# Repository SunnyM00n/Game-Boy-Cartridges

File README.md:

# Game Boy Cartridge Circuit Boards

This is a repository listing all of my Game Boy game circuit board variants. <a href="https://github.com/MouseBiteLabs/Game-Boy-Cartridges/wiki">Also be sure to check out the wiki for more information.</a>

## Game Boy Board Links

| **Board Name**                                                                                                                | **Board Number**   | **Max ROM Size**       | **Max RAM Size**  | **Multicart Support?** | **Memory Family Used**          |
|-------------------------------------------------------------------------------------------------------------------------------|--------------------|------------------------|-------------------|------------------------|---------------------------------|
| <a href="https://github.com/MouseBiteLabs/Game-Boy-MBC1-Cartridge">MBC1 (Type B)</a>                                          | GB-4DV4S-01B       | 4 MB                   | 32 KB             | No                     | Type B (29F016, 29F032, 29F033) |
| <a href="https://github.com/MouseBiteLabs/Game-Boy-MBC3-Cartridge">MBC3 (Type B)</a>                                          | GB-4KV4S-01B       | 4 MB                   | 32 KB             | No                     | Type B (29F016, 29F032, 29F033) |
| <a href="https://github.com/MouseBiteLabs/Game-Boy-MBC5-Cartridge">MBC5 (Type B)</a>                                          | GB-4AV8S-01B       | 4 MB                   | 128 KB            | No                     | Type B (29F016, 29F032, 29F033) |
| <a href="https://github.com/MouseBiteLabs/Game-Boy-Cartridges/tree/main/MBC3%20Multicart">MBC3 Multicart (Type B)</a>         | GB-4KV8Q-01B       | 4 MB (2x 2 MB, 4x 1MB) | 128 KB (4x 32 KB) | Yes                    | Type B (29F032, 29F033)         |
| <a href="https://github.com/MouseBiteLabs/Game-Boy-Cartridges/tree/main/MBC5%20Multicart">MBC5 Multicart (Type B)</a>         | GB-4AV8Q-01B       | 4 MB (2x 2 MB, 4x 1MB) | 128 KB (4x 32 KB) | Yes                    | Type B (29F032, 29F033)         |
| <a href="https://github.com/MouseBiteLabs/Game-Boy-Cartridges/tree/main/MBC1%20(Type%20A%2C%20SRAM)">MBC1 (Type A)</a>        | GB-2DV4S-01A       | 2 MB                   | 32 KB             | No                     | Type A (M29F160)                |
| <a href="https://github.com/MouseBiteLabs/Game-Boy-Cartridges/tree/main/MBC3%20(Type%20A%2C%20SRAM)">MBC3 (Type A)</a>        | GB-2KV4S-01A       | 2 MB                   | 32 KB             | No                     | Type A (M29F160)                |
| <a href="https://github.com/MouseBiteLabs/Game-Boy-Cartridges/tree/main/MBC5%20(Type%20A%2C%20SRAM)">MBC5 (Type A)</a>        | GB-2AV8S-01A       | 2 MB                   | 128 KB            | No                     | Type A (M29F160)                |
| MBC1 (Type A, FRAM)                                                                                                           | GB-2DF4S-01A       | 2 MB                   | 32 KB             | No                     | Type A (M29F160)                |
| <a href="https://github.com/MouseBiteLabs/Game-Boy-Cartridges/tree/main/MBC3%20(Type%20A%2C%20FRAM)">MBC3 (Type A, FRAM)</a>  | GB-2KF4S-01A       | 2 MB                   | 32 KB             | No                     | Type A (M29F160)                |
| <a href="https://github.com/MouseBiteLabs/Game-Boy-Cartridges/tree/main/MBC5%20(Type%20A%2C%20FRAM)">MBC5 (Type A, FRAM)</a>  | GB-2AF4S-01A       | 2 MB                   | 32 KB             | No                     | Type A (M29F160)                |

## Naming Convention

| GB       | \- | 2                 | A               | V              | 4            | S                                            | \- | 01       | A                                       |
| -------- | -- | ----------------- | --------------- | -------------- | ------------ | -------------------------------------------- | -- | -------- | --------------------------------------- |
| Game Boy |    | Max ROM Size (MB) | Mapper Chip     | SRAM or FRAM?  | Max RAM Size | Multicart Support                            |    | Revision | Memory Family                           |
|          |    | 1                 | N = None        | X = None       | 0 = None     | S = Single game                              |    |          | A = New EEPROM (M29F160)                |
|          |    | 2                 | D = MBC1        | V = SRAM       | 1 = 2 KB     | D = Multicart (2x, split max ROM/RAM space)  |    |          | B = NOS EEPROM (29F016, 29F032, 29F033) |
|          |    | 4                 | K = MBC3        | F = FRAM       | 2 = 8 KB     | Q = Multicart (4x, split max ROM/RAM space)  |    |          |                                         |
|          |    | 6                 | A = MBC5        |                | 4 = 32 KB    |                                              |    |          |                                         |
|          |    | 8                 |                 |                | 8 = 128 KB   |                                              |    |          |                                         |

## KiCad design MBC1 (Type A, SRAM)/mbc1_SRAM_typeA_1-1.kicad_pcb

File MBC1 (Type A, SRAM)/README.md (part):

# Game Boy MBC1 Cartridge - Type A, SRAM

This is an updated design of my flashable MBC1-based cartridge for the Game Boy. The MBC1 mapper was used in many of the earlier Game Boy games, such as the Super Mario Land series, the Donkey Kong Land series, Metroid II, and one of my personal favorites - the original Link's Awakening. 

**This MBC1 cartridge uses brand new M29F160 EEPROM chips and battery-backed SRAM.**

This circuit board should cover most, if not all, MBC1 games. The features are as follows:

- Able to make games that use 512 KB (4 Mbit) of ROM and 256 Kbit of RAM, or 2 MB (16 Mbit) of ROM and 64 Kbit of RAM
- Compatibility with all four of the major Game Boy battery management ICs - MM1026, MM1134, BA6129, and BA6735
- The option to add battery backup to the cartridge *without* the need of the original battery management ICs - perfect for MBC1 donors that didn't have batteries in them
- Lower battery consumption compared to some of the original cartridges
- Fully compatible with the <a href="https://www.gbxcart.com/">GBxCart RW</a> so you can transfer games and save files to and from the board

All gerbers and source files can be found in this repo, as this project is fully open source **with attribution**.

## Important Version Note!

An error with v1.0 boards does not let you flash games on an assembled cart with the RAM set to 64K mode. Functionally, this means you cannot flash game ROMs larger than 512Kbit. I can find only one game that fits this category, so this should be a very minor issue. 

**You must put the cartridge in 256K SRAM mode in order to flash any game using a cart flasher like the GBxCart. Once your game is flashed, change the RAM mode to 64K if your game requires it.** You can also flash the ROM to the M29F160 separately, and then solder it onto the board, to get around this issue.

Version 1.1 should fix this error, but it has not been tested yet. I am waiting for the order of boards to arrive so I may test it.

## Important Things Before You Start

1) To use this board, you need to have an original Game Boy game that uses an MBC1 mapper chip. <a href="https://catskull.net/gb-rom-database/">You can find a list of games and their mappers here</a>. Use the search function. Please note the RAM is in bytes, not bits. Since SRAM in this repo is defined in bits, you need to convert by multiplying the number of bytes by 8.
2) You will need to remove the MBC1 from your donor cartridge for use on this board. This will require a hot air rework station or a hot plate. There's a list below of other parts you can re-use from the donor cartridge.
3) When soldering parts on, it's a good idea to put kapton tape or otherwise cover the bottom cartridge edge. You do not want to get solder on the cartridge contacts.
4) I am not responsible for any damage you do to your self or your property. Attempt this project at your own risk.
5) I do not guarantee design compatibility. You may encounter issues with certain games. There is also a chance I have made an error in the design or the BOM - if this is the case, I will do everything I can to address the problem as quickly as possible.
6) If you are using this board to make games other than for personal use, you must have permission from the originator to use and distribute any ROM images or other related material. You are responsible for making sure you adhere to any license requirements.

DO NOT use my circuit boards for profiting from stolen work - this especially includes homebrew content, ROM hacks, and using fan-made labels without permission from the originator. **Support original creators!**

## Board Characteristics and Order Information

The zipped folder contains all the gerber files for this board. The following options **must** be chosen when ordering boards for yourself.

- Thickness: 0.8mm
- Surface Finish: ENIG
- Gold Fingers: Yes, 30° chamfer

**I sell this blank circuit board on Etsy, so you don't have to buy a bunch of multiples if you don't want to.** (Click the banner!)

You can use the zipped folder at any board fabricator you like. You may also buy the board from PCBWay using this link (disclosure: I receive 10% of the sale value to go twoards future PCB orders of my own):

<a href="https://oshpark.com/shared_projects/nTwQT1IF">The board is also listed on OSH Park as well.</a> **Be sure to get them in 0.8mm thickness if you order from here.**

## Required Equipment

The EEPROM on the board needs to be programmed somehow. There are a few options for doing this:

1) <a href="https://www.gbxcart.com/">**GBxCart**</a>. This is a perfect option if you want an easy way to make Game Boy cartridges without a lot of extra effort. This is a standalone flasher that plugs into your computer via USB. The cartridge circuit board is fully compatible with it, and it makes reflashing games extremely easy using <a href="https://github.com/lesserkuma/FlashGBX">lesserkuma's FlashGBX software</a>.
2) At the lowest level, you can buy an EEPROM programmer with a TSOP chip programming adapter. The downside to this method is that you have to desolder the chip every time you want to program it. The <a href="https://flashcatusb.com/">FlashcatUSB</a> is one popular option in retro spaces, but I use the <a href="https://xgecu.myshopify.com/products/xgecu-new-t48-tl866-3gprogrammer-v12-01-support-28000-ics-for-spi-nor-nand-flash-emmc-bga153-162-169-100-221-tsop-sop-plcc">T48 programmer</a> with the <a href="https://xgecu.myshopify.com/products/100-original-xgecu-adp_f48_ex-1-tsop48-special-adapter-for-nor-flash-only-use-on-t48-tl866-3g-programmer">TSOP48 adapter</a>.

### How to Program the Cartridges

<a href="https://github.com/MouseBiteLabs/Game-Boy-Cartridges/wiki">Check out the wiki for more information.</a>

## Battery Safety

When assembling a board, I recommend populating all the parts *except* the battery, and getting it to run initially without it. This is to make it easier to fix any solder connections that might need fixing, without having to worry about getting the battery hot. And if you need to rework anything near the battery after you've put it on the board, be safe and remove it before putting a hot soldering iron next to it.

If you're assembling these boards with a hot plate or hot air, *do not* solder the battery on this way. You should use an iron, and keep heat off of the battery as much as possible. 

(Also check polarity!)

## Board Configurations

The board comes with four sets of jumper pads for solder bridges. SJ1 and SJ2 require you to solder bridge the middle pad either to the top pad or the bottom pad. SJ3 and SJ4 are configured by either leaving them alone or bridging them with solder. Here are the situations where you need to add solder bridges.

**<a href="https://github.com/MouseBiteLabs/Game-Boy-Cartridges/wiki/MBC1">You can check out the wiki for some pictures of boards in various configurations to follow along with.</a>**

### RAM Size Selection (SJ1/SJ2, or SW1)

These two sets of pads are labelled "RAM SIZE" in the middle of the board. Soldering them will configure the max RAM *and* ROM size. You must configure these pads for every game you make - do not leave them empty (if you have no SRAM, solder to the "64K" setting to maximize ROM space). <a href="https://catskull.net/gb-rom-database/">You can find a list of games here with their respective ROM and RAM sizes.</a>

**As stated earlier, on v1.0 boards, the RAM size selection must be in 256K mode to flash your ROM file with a cart flasher.**

- Solder bridge SJ1 and SJ2 from their middle pads to the top pads for games that have larger ROM sizes (up to 2 MB, or 16 Mbit of ROM, and up to 64 Kbit of RAM).

- Solder bridge SJ1 and SJ2 from their middle pads to the bottom pads for games that have larger RAM sizes (up to 512 KB, or 4 Mbit of ROM, and up to 256 Kbit of RAM).

- SJ1 and SJ2 must be soldered in the same direction.

- The footprint of these selection pads should allow for a DPDT switch, part number CAS-220A1, to be placed on these pads instead of having to bridge the pads with solder.

### Using an MM1134 or BA6735 for U4 (SJ3)

Bridge the jumper SJ3 if you have either an MM1134 or BA6735 for U4, specifically. Any other battery management IC must leave SJ3 unsoldered.

### Making Games Without RAM (SJ1/SJ2, SJ4)

If your game does not have RAM on it (and therefore, you don't need the battery management IC U4), bridge SJ4 with solder. **Do not** bridge SJ4 if you are using U5 (TPS3613) instead of U4.

You also should solder the SRAM size selection to the 64K setting.

## Test Points and Final Checkout

On the back of the board are five test points. Here's where they are connected:

- TP1: SRAM supply voltage
- TP2: Battery voltage (after R1)
- TP3: Battery voltage (positive terminal of battery)
- TP4: Ground
- TP5: VCC input voltage

After you assemble your game, you should measure the current out of the battery. But first, you should program it with the GBxCart, or if you programmed the EEPROM separately, put it into a Game Boy and cycle power once. Then, flip the PCB upside down on a non-conductive surface (not your leg), and set your multimeter in DC millivolts (or volts). Put the positive probe on TP3 and the negative probe on TP2. If you used a 10kΩ for R1, as indicated in the BOM, you should read a voltage in the single of millivolts. If you have something much higher, especially voltages above 20mV, then you likely have an issue or short circuit on the board somewhere.

**Note: You need to power up the game at least once before battery currents will make sense - the battery management ICs can start up in an unknown state before applying main power to the board.**

To estimate battery life, see <a href="https://github.com/MouseBiteLabs/Game-Boy-MBC1-Cartridge/tree/main/Technical#estimating-battery-life">this section in the Technical Design Document of my first MBC1 design</a>, or for more in-depth analysis, <a href="https://hackaday.io/project/11864-tritiled/log/72554-determining-maximum-runtime-176-to-202-years-cr2032">this Hackaday post</a>.

## Board Fitment

The shape of this board was originally meant to mimic original Game Boy circuit boards as closely as possible. Unfortunately, when placed in some aftermarket Game Boy cartridge shells (like those from Cloud Game Store), the circuit board has a lot of freedom to rotate around the main screw hole in the bottom-middle of the cartridge. This can cause misalignment when you put it in a Game Boy, which can cause a game to either not load properly (garbled Game Boy logo) or shut off the Game Boy because of a short circuit. This isn't *dangerous* or anything, just annoying.

In order to make the boards fit nicer in any kind of shell, I added extended tabs of circuit board material to the edges of the cartridges to keep it from rotating too much in shells, which was suggested to me by <a href="https://github.com/orangeglo">orangeglo</a>! (Thanks!)

If you're having trouble fitting the circuit board into a shell, because the tabs interfere with the cart edges, you can safely sand or trim them down as there is no copper within the tabs themselves. The only shell that appears to require any kind of trimming are Kitsch-Bent shells.

## Bill of Materials (BOM)

Your parts list will vary depending on the game you are trying to make, and what chips you have for the battery management (if any). **You cannot use both U4 and U5 - you must choose one or the other.** U4 comes from a donor cartridge, and U5 is a readily available aftermarket option.

Please carefully review the parts you need for the board you are trying to make. Do not add any parts to your build that don't appear in the column for the game you are making. This means you *cannot* populate every component on the board at the same time.

| Reference Designators | Value/Part Number              | Package          | Description        | No save carts | Save carts with MM1134 or BA6735 | Save carts with MM1026 or BA6129 | Save carts without donor U4 chip | Source                                           |
| --------------------- | ------------------------------ | ---------------- | ------------------ | ------------- | -------------------------------- | -------------------------------- | -------------------------------- | ------------------------------------------------ |
| B1                    | CR2032, CR2025, CR2016         | CR2032           | Backup Battery     |               | x                                | x                                | x                                | [https://mou.sr/3SeAzfT](https://mou.sr/3SeAzfT) |
| C1                    | 0.1uF                          | 0603             | Capacitor (MLCC)   | x             | x                                | x                                | x                                | [https://mou.sr/3ENc15O](https://mou.sr/3ENc15O) |
| C4                    | 0.1uF                          | 0603             | Capacitor (MLCC)   |               | x                                | x                                |                                  | [https://mou.sr/3ENc15O](https://mou.sr/3ENc15O) |
| C5                    | 0.1uF                          | 0603             | Capacitor (MLCC)   |               | x                                | x                                | x                                | [https://mou.sr/3ENc15O](https://mou.sr/3ENc15O) |
| C6                    | 10uF                           | 0603             | Capacitor (MLCC)   |               | x                                | x                                | x                                | [https://mou.sr/3mZtSkF](https://mou.sr/3mZtSkF) |
| C7                    | 0.1uF                          | 0603             | Capacitor (MLCC)   | x             | x                                | x                                | x                                | [https://mou.sr/3ENc15O](https://mou.sr/3ENc15O) |
| C8                    | 0.1uF                          | 0603             | Capacitor (MLCC)   |               |                                  |                                  | x                                | [https://mou.sr/3ENc15O](https://mou.sr/3ENc15O) |
| Q1                    | 2N7002                         | SOT-23           | N-Channel FET      |               |                                  |                                  | x                                | [https://mou.sr/3rgfh6J](https://mou.sr/3rgfh6J) |
| Q2                    | 2N7002                         | SOT-23           | N-Channel FET      |               |                                  | x                                |                                  | [https://mou.sr/3rgfh6J](https://mou.sr/3rgfh6J) |
| R1                    | 10k                            | 0603             | Resistor           |               | x                                | x                                | x                                | [https://mou.sr/3riR7IH](https://mou.sr/3riR7IH) |
| R3                    | 49.9k                          | 0603             | Resistor           |               | x                                | x                                | x                                | https://mou.sr/3Q3NRZO                           |
| R4                    | 49.9k                          | 0603             | Resistor           |               | x                                | x                                | x                                | https://mou.sr/3Q3NRZO                           |
| R5                    | 49.9k                          | 0603             | Resistor           |               | x                                | x                                | x                                | https://mou.sr/3Q3NRZO                           |
| R6                    | 49.9k                          | 0603             | Resistor           |               | x                                | x                                | x                                | https://mou.sr/3Q3NRZO                           |
| R7                    | 10k                            | 0603             | Resistor           |               |                                  | x                                |                                  | [https://mou.sr/3riR7IH](https://mou.sr/3riR7IH) |
| R8                    | 10k                            | 0603             | Resistor (v1.1 and later) | x      | x                                | x                                | x                                | [https://mou.sr/3riR7IH](https://mou.sr/3riR7IH) |
| R9                    | 130k                           | 0603             | Resistor           |               |                                  |                                  | x                                | https://mou.sr/3MjXliy                           |
| R10                   | 49.9k                          | 0603             | Resistor           |               |                                  |                                  | x                                | https://mou.sr/3Q3NRZO                           |
| U1                    | M29F160                        | TSOP-48          | Flash EEPROM       | x             | x                                | x                                | x                                | [https://mou.sr/3N0a9eL](https://mou.sr/3N0a9eL) |
| U2                    | MBC1                           | SOP-24           | MBC1 Mapper        | x             | x                                | x                                | x                                | Donor MBC1 Game Boy cartridge                    |
| U3                    | AS6C6264, AS6C62256            | SOP-28           | SRAM               |               | x                                | x                                | x                                | [https://mou.sr/450klcY](https://mou.sr/450klcY) |
| U4                    | MM1026, MM1134, BA6129, BA6735 | SOIC-8           | Battery Management |               | x                                | x                                |                                  | Donor Game Boy cartridge                         |
| U5                    | TPS3613                        | MSOP-10          | Battery Management |               |                                  |                                  | x                                | https://mou.sr/45Ir2kh                           |

*Note that C9 - C11 footprints are only included on the board for strange edge cases that may require them sometime in the future; do not populate! See the technical design document for more information.*

### Usable Donor Cartridge Parts

You can use a few parts from the donor cart on the new board to save some money. Note that you will generally get better reliability with new parts as opposed to old ones. For example: I have seen failed RAM chips from donors in the past.

1) **U2: MBC1** - This one is required
2) **U3: SRAM** - You can use this part *only if* the game you're making uses the same or less amount of RAM that the donor cartridge does
3) **U4: Battery Management IC** - Using this is probably preferred over the TPS3613 because it'll save you money and parts to put on

You could probably transfer over most of the 0.1uF capacitors but they're pretty cheap anyway, so I generally just recommend buying new resistors and capacitors.

## Things to Remember

- The footprint for the battery can fit a CR2032, CR2025, or CR2016 with solder tabs. The only difference is the mAh capacity (larger number = longer life). If you get Panasonic tabbed batteries, you may have to trim the battery tabs to make them fit on the footprint.
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
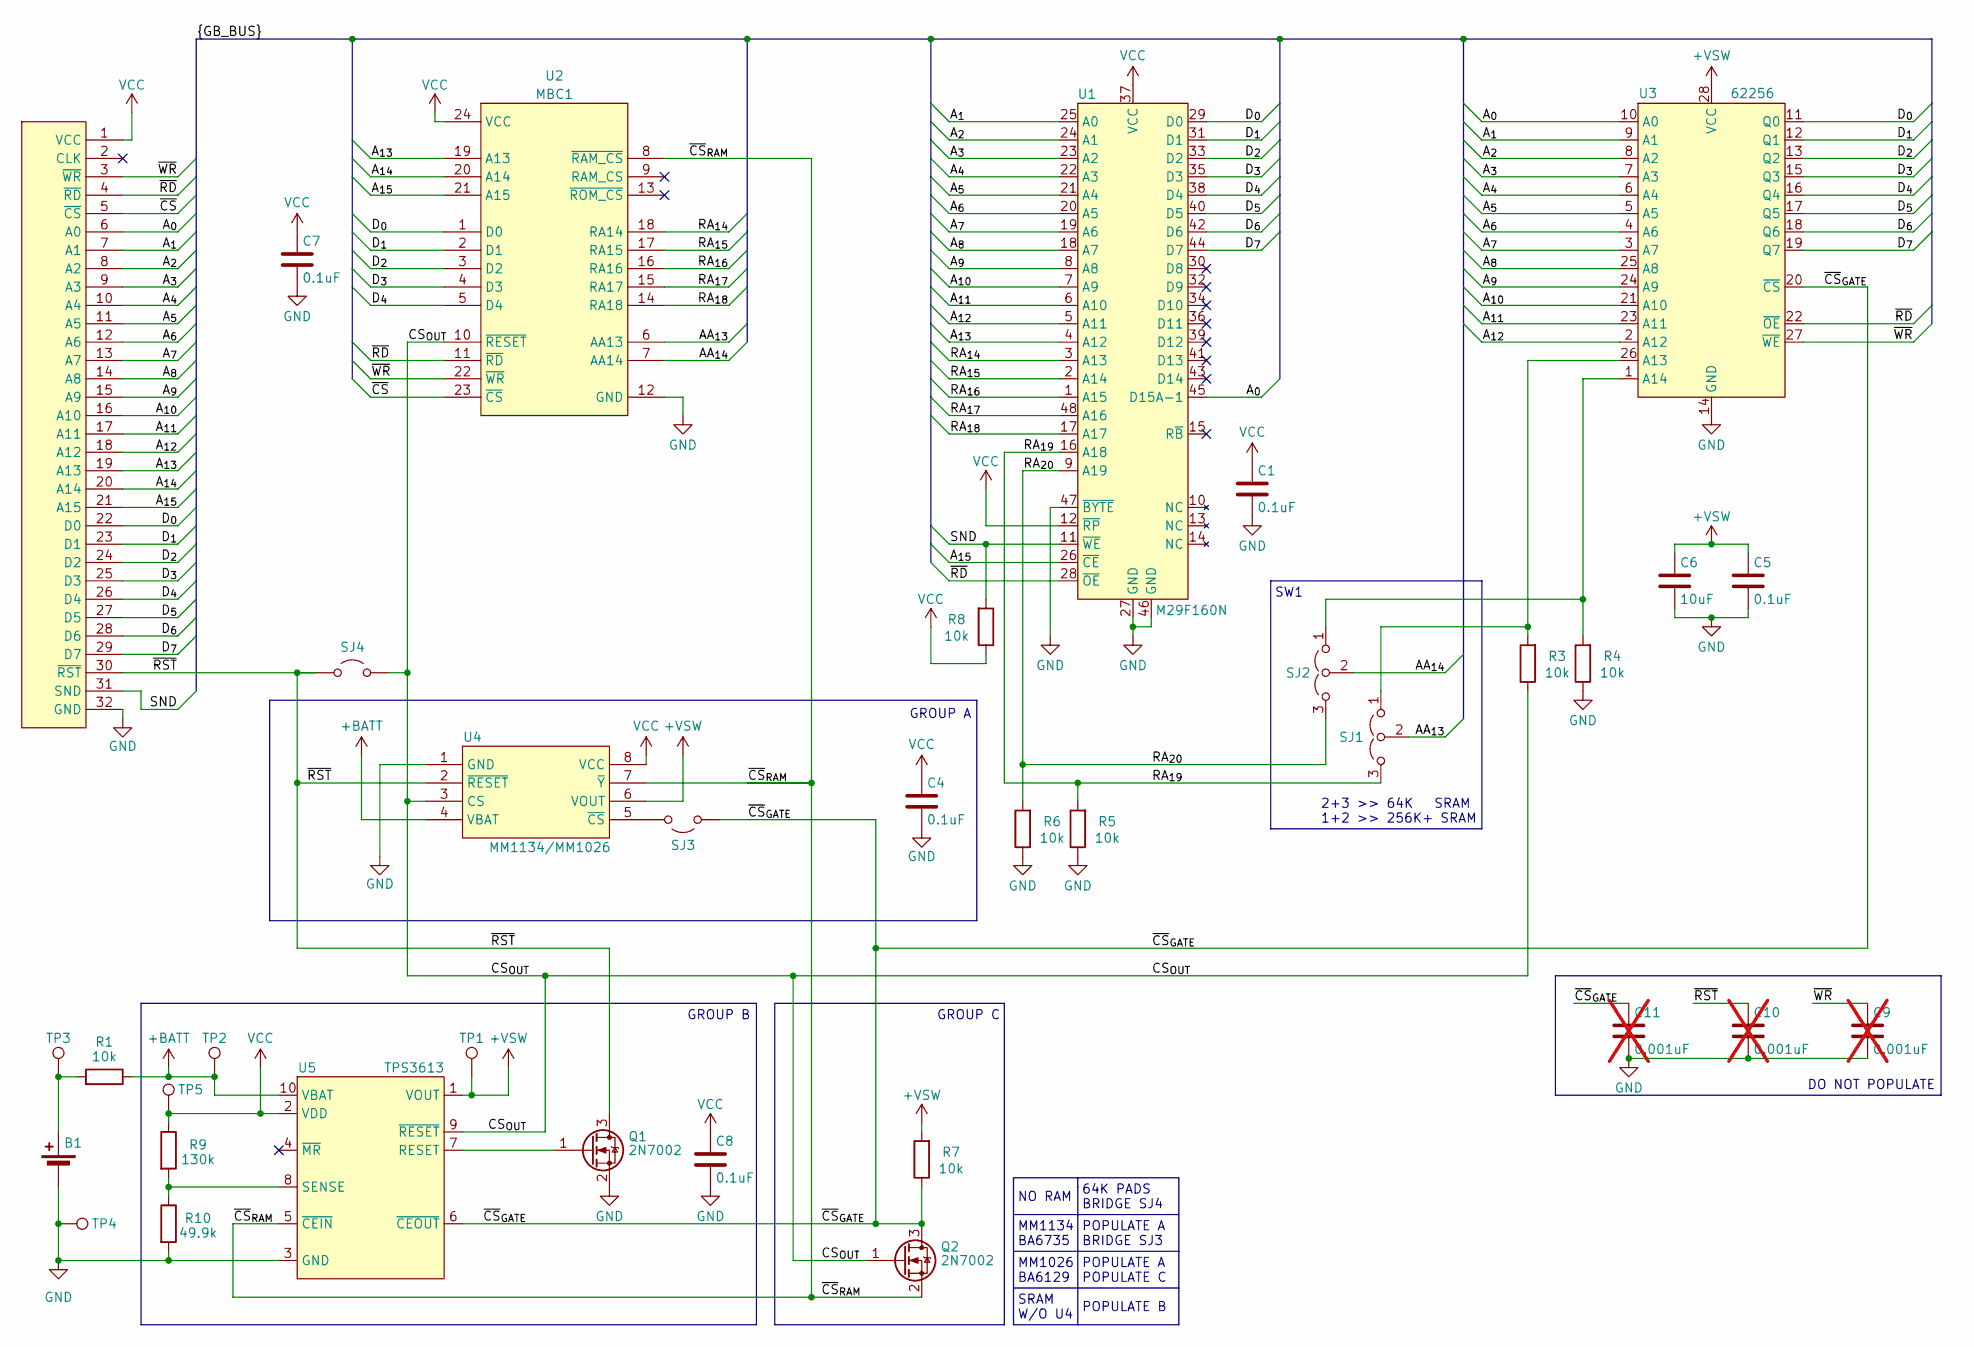
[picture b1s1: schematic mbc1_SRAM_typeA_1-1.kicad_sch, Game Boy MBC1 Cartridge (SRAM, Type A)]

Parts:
B1: CR2025
C1, C4, C5, C7, C8: 0.1uF; C_0603_1608Metric_Boxed
C6: 10uF; C_0603_1608Metric_Boxed
C9, C10, C11: 0.001uF; C_0603_1608Metric_Boxed; not fitted
P1: GBC_CARTTAB; GBC_CART_TABBED
Q1, Q2: 2N7002; SOT-23
R1, R3, R4, R5, R6, R7, R8: 10k; R_0603_1608Metric_Boxed
R9: 130k; R_0603_1608Metric_Boxed
R10: 49.9k; R_0603_1608Metric_Boxed
SJ1, SJ2: SJ2W; SJ_2
SJ3, SJ4: SJ
TP1, TP2, TP3, TP4, TP5: TPB1,27; TestPoint_Pad_D1.0mm
U1: M29F160N; TSOP-I-48_18.4x12mm_P0.5mm
U2: MBC1; SO24
U3: 62256; SO28
U4: MM1134/MM1026; SOIC-8_3.9x4.9mm_P1.27mm
U5: TPS3613; MSOP-10_3x3mm_P0.5mm

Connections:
+BATT: R1.1, TP2.1, U4.4 (VBAT), U5.10 (VBAT)
+VSW: C5.1, C6.1, R7.2, TP1.1, U3.28 (VCC), U4.6 (VOUT), U5.1 (VOUT)
/AA_{13}: SJ1.2 (C), U2.6 (AA13)
/AA_{14}: SJ2.2 (C), U2.7 (AA14)
/A_{0}: P1.6 (A0), U1.45 (D15A-1), U3.10 (A0)
/A_{1}: P1.7 (A1), U1.25 (A0), U3.9 (A1)
/A_{2}: P1.8 (A2), U1.24 (A1), U3.8 (A2)
/A_{3}: P1.9 (A3), U1.23 (A2), U3.7 (A3)
/A_{4}: P1.10 (A4), U1.22 (A3), U3.6 (A4)
/A_{5}: P1.11 (A5), U1.21 (A4), U3.5 (A5)
/A_{6}: P1.12 (A6), U1.20 (A5), U3.4 (A6)
/A_{7}: P1.13 (A7), U1.19 (A6), U3.3 (A7)
/A_{8}: P1.14 (A8), U1.18 (A7), U3.25 (A8)
/A_{9}: P1.15 (A9), U1.8 (A8), U3.24 (A9)
/A_{10}: P1.16 (A10), U1.7 (A9), U3.21 (A10)
/A_{11}: P1.17 (A11), U1.6 (A10), U3.23 (A11)
/A_{12}: P1.18 (A12), U1.5 (A11), U3.2 (A12)
/A_{13}: P1.19 (A13), U1.4 (A12), U2.19 (A13)
/A_{14}: P1.20 (A14), U2.20 (A14)
/A_{15}: P1.21 (A15), U1.26 (~CE), U2.21 (A15)
/CS_{OUT}: Q2.1 (G), R3.1, SJ4.2 (B), U2.10 (~RESET), U4.3 (CS), U5.9 (~RESET)
/D_{0}: P1.22 (D0), U1.29 (D0), U2.1 (D0), U3.11 (Q0)
/D_{1}: P1.23 (D1), U1.31 (D1), U2.2 (D1), U3.12 (Q1)
/D_{2}: P1.24 (D2), U1.33 (D2), U2.3 (D2), U3.13 (Q2)
/D_{3}: P1.25 (D3), U1.35 (D3), U2.4 (D3), U3.15 (Q3)
/D_{4}: P1.26 (D4), U1.38 (D4), U2.5 (D4), U3.16 (Q4)
/D_{5}: P1.27 (D5), U1.40 (D5), U3.17 (Q5)
/D_{6}: P1.28 (D6), U1.42 (D6), U3.18 (Q6)
/D_{7}: P1.29 (D7), U1.44 (D7), U3.19 (Q7)
/RA_{14}: U1.3 (A13), U2.18 (RA14)
/RA_{15}: U1.2 (A14), U2.17 (RA15)
/RA_{16}: U1.1 (A15), U2.16 (RA16)
/RA_{17}: U1.48 (A16), U2.15 (RA17)
/RA_{18}: U1.17 (A17), U2.14 (RA18)
/RA_{19}: R5.2, SJ1.3 (B), U1.16 (A18)
/RA_{20}: R6.2, SJ2.3 (B), U1.9 (A19)
/SND: P1.31 (SND), R8.2, U1.11 (~WE)
/~CS: P1.5 (~CS), U2.23 (~CS)
/~CS_{GATE}: C11.1, Q2.3 (D), R7.1, SJ3.2 (B), U3.20 (~CS), U5.6 (~CEOUT)
/~CS_{RAM}: Q2.2 (S), U2.8 (~RAM_CS), U4.7 (~Y), U5.5 (~CEIN)
/~RD: P1.4 (~RD), U1.28 (~OE), U2.11 (~RD), U3.22 (~OE)
/~RST: C10.1, P1.30 (~RST), Q1.3 (D), SJ4.1 (A), U4.2 (~RESET)
/~WR: C9.1, P1.3 (~WR), U2.22 (~WR), U3.27 (~WE)
GND: B1.2 (-), C1.2, C4.2, C5.2, C6.2, C7.2, C8.2, C9.2, C10.2, C11.2, P1.32 (GND), Q1.2 (S), R4.1, R5.1, R6.1, R10.2, TP4.1, U1.27 (GND), U1.46 (GND), U1.47 (~BYTE), U2.12 (GND), U3.14 (GND), U4.1 (GND), U5.3 (GND)
unnamed: B1.1 (+), R1.2, TP3.1
unnamed: Q1.1 (G), U5.7 (RESET)
unnamed: R3.2, SJ1.1 (A), U3.26 (A13)
unnamed: R4.2, SJ2.1 (A), U3.1 (A14)
unnamed: SJ3.1 (A), U4.5 (~CS)
unnamed: R9.2, R10.1, U5.8 (SENSE)
VCC: C1.1, C4.1, C7.1, C8.1, P1.1 (VCC), R8.1, R9.1, TP5.1, U1.12 (~RP), U1.37 (VCC), U2.24 (VCC), U4.8 (VCC), U5.2 (VDD)

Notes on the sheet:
GROUP A
POPULATE A POPULATE C
SW1
BRIDGE SJ4
POPULATE A BRIDGE SJ3
2+3 >> 64K SRAM 1+2 >> 256K+ SRAM
MM1134 BA6735
DO NOT POPULATE
SRAM W/O U4
GROUP C
POPULATE B
MM1026 BA6129
GROUP B
64K PADS
NO RAM

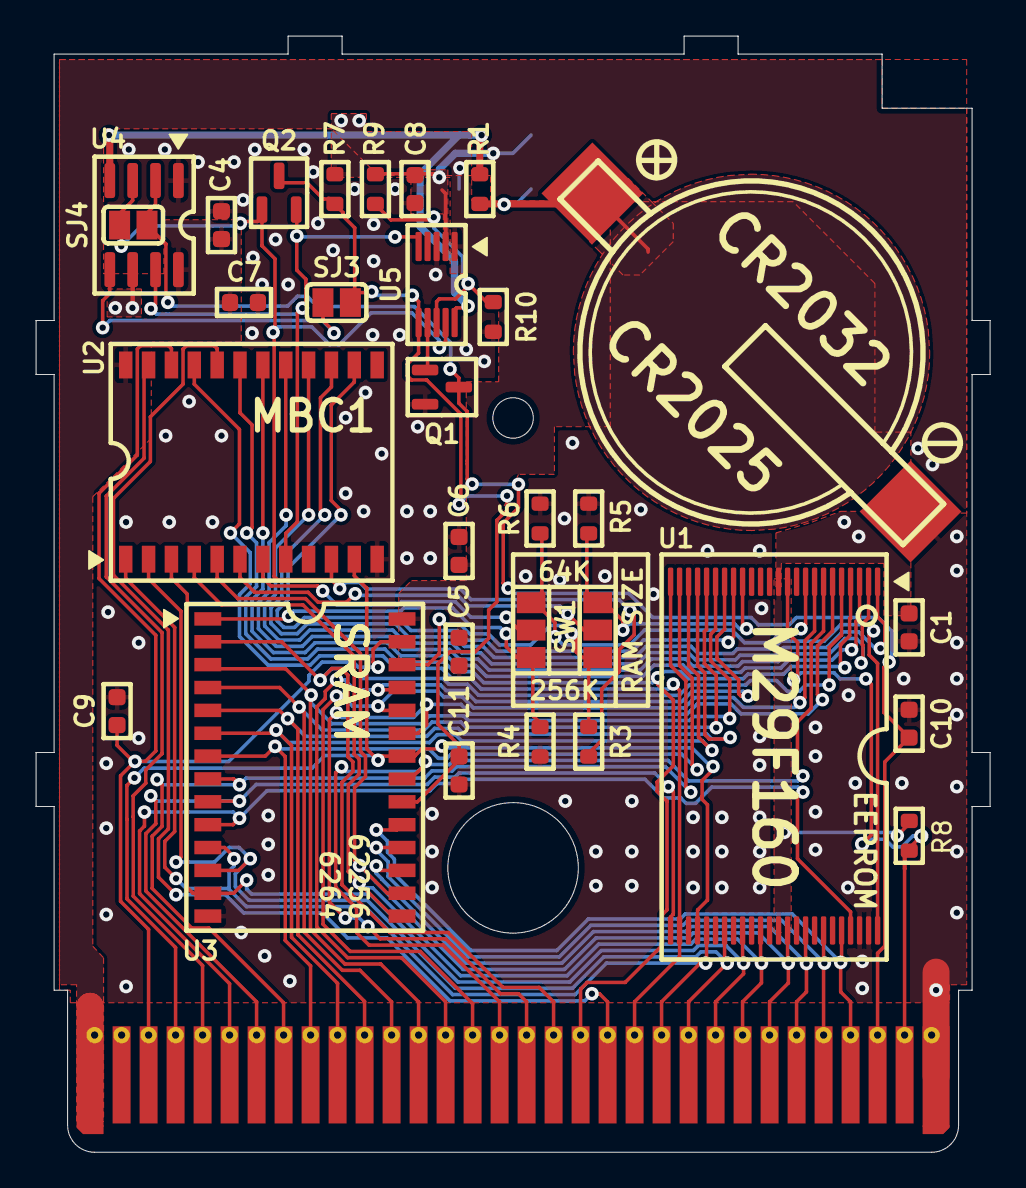
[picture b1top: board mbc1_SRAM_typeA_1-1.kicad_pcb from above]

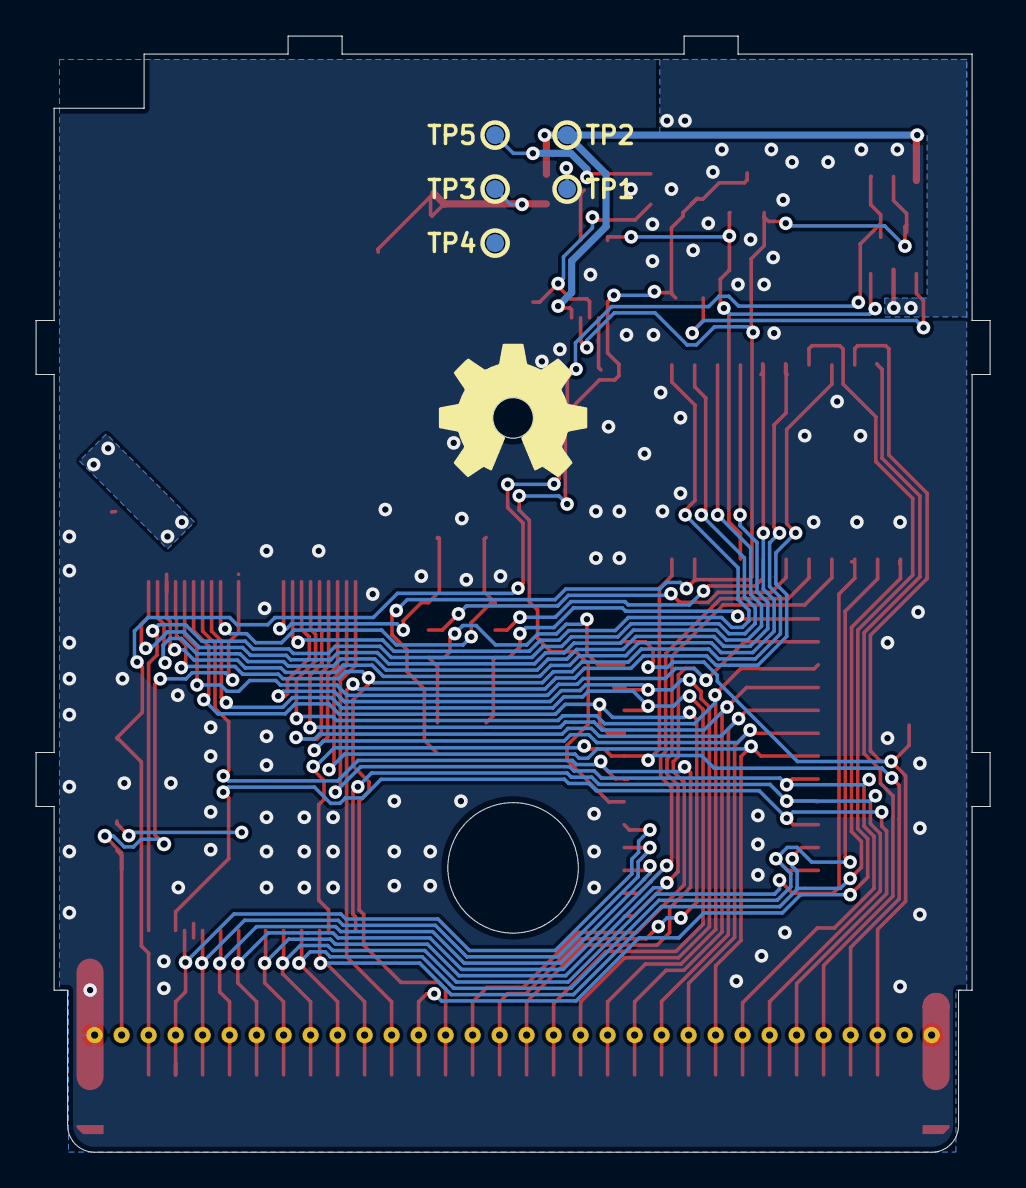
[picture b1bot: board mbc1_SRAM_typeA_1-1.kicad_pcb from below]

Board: 2 copper layers, 53.0 x 62.0 mm, 36 parts (5 on the bottom side), 51 nets.

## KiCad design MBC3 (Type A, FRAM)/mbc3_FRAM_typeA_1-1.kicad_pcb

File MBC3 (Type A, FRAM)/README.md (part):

# Game Boy MBC3 Cartridge - Type A, FRAM

# DESIGN IS UNVERIFIED (but probably ok)

This is an alternate design of my <a href="https://github.com/MouseBiteLabs/Game-Boy-Cartridges/tree/main/MBC3%20(Type%20A%2C%20SRAM)">flashable MBC3-based cartridge for the Game Boy</a>. This board uses non-volatile FRAM instead of SRAM to hold save data. I made this specifically for use with the <a href="https://github.com/MouseBiteLabs/Super-Game-Boy-Plus/tree/main">Super Game Boy Plus boards.</a> Even though the board uses FRAM for the save data, the real-time clock data is stored on the MBC3 chip itself, and therefore a battery is included to keep the MBC3 powered on while the Game Boy is off, to keep the time in memory. If the battery dies, your save data will still be available on the FRAM chip, meaning swapping a dead battery to restore clock function will not risk any save data.

**This MBC3 cartridge uses brand new M29F160 EEPROM chips and non-volatile FRAM.**

This circuit board should cover most MBC3 games, and is able to make games up to 2 MB in size, that use up to 256 Kbit of RAM. It is fully compatible with both the <a href="https://www.gbxcart.com/">GBxCart RW</a> and sanni's <a href="https://github.com/sanni/cartreader">Open Source Cart Reader (OSCR)</a> so you can transfer games and save files to and from the board. Because of the FRAM this board utilizes, <a href="https://github.com/MouseBiteLabs/Game-Boy-Cartridges/tree/main/MBC3%20(Type%20A%2C%20SRAM)#why-not-fram">it is technically only fully compatible with regular Game Boy games, and not Game Boy Color games,</a> though no issues have been reported in the past when using them with Game Boy Color games.

All gerbers and source files can be found in this repo, as this project is fully open source.

## Important Things Before You Start

1) To use this board, you need to have an original Game Boy game that uses an MBC3 mapper chip. <a href="https://catskull.net/gb-rom-database/">You can find a list of games and their mappers here</a>. Use the search function. Please note the RAM is in bytes, not bits. Since RAM in this repo is defined in bits, you need to convert by multiplying the number of bytes by 8.
2) You will need to remove the MBC3 from your donor cartridge for use on this board. This will require a hot air rework station or a hot plate. There's a list below of other parts you can re-use from the donor cartridge.
3) When soldering parts on, it's a good idea to put kapton tape or otherwise cover the bottom cartridge edge. You do not want to get solder on the cartridge contacts.
4) I am not responsible for any damage you do to your self or your property. Attempt this project at your own risk.
5) I do not guarantee design compatibility. You may encounter issues with certain games. There is also a chance I have made an error in the design or the BOM - if this is the case, I will do everything I can to address the problem as quickly as possible.
6) If you are using this board to make games other than for personal use, you must have permission from the originator to use and distribute any ROM images or other related material. You are responsible for making sure you adhere to any license requirements.

DO NOT use my circuit boards for profiting from stolen work - this especially includes homebrew content, ROM hacks, and using fan-made labels without permission from the originator. **Support original creators!**

## Board Characteristics and Order Information

The zipped folder contains all the gerber files for this board. The following options **must** be chosen when ordering boards for yourself.

- Thickness: 0.8mm
- Surface Finish: ENIG
- Gold Fingers: Yes, 30° chamfer

**I sell this blank circuit board on Etsy, so you don't have to buy a bunch of multiples if you don't want to.** (Click the banner!)

(Not yet available - this is a placeholder.)

You can use the zipped folder at any board fabricator you like. You may also buy the board from PCBWay using this link (disclosure: I receive 10% of the sale value to go towards future PCB orders of my own):

<a href="https://oshpark.com/shared_projects/Hw9rGuT9">The board is also listed on OSH Park as well.</a> **Be sure to get them in 0.8mm thickness if you order from here.**

## Required Equipment

The EEPROM on the board needs to be programmed somehow. There are a few options for doing this:

1) <a href="https://www.gbxcart.com/">**GBxCart**</a>. This is a perfect option if you want an easy way to make Game Boy cartridges without a lot of extra effort. This is a standalone flasher that plugs into your computer via USB. The cartridge circuit board is fully compatible with it, and it makes reflashing games extremely easy using <a href="https://github.com/lesserkuma/FlashGBX">lesserkuma's FlashGBX software</a>.
2) <a href="https://github.com/sanni/cartreader">**OSCR**</a> by sanni. This is the Open Source Cart Reader, capable of making backups of both the ROM and RAM contents of cartridges across many different systems - like the NES, SNES, Genesis, and of course Game Boy and Game Boy Advance. And you can also use it to flash these Game Boy cartridges. The OSCR however requires assembly (or someone to assemble it for you) and is a bit more cumbersome to interface with on a PC, but it's an extremely powerful tool that I can't recommend enough if you want to expand past Game Boys.
3) At the lowest level, you can buy an EEPROM programmer with a TSOP chip programming adapter. The downside to this method is that you have to desolder the chip every time you want to program it. The <a href="https://flashcatusb.com/">FlashcatUSB</a> is one popular option in retro spaces, but I use the <a href="https://xgecu.myshopify.com/products/xgecu-new-t48-tl866-3gprogrammer-v12-01-support-28000-ics-for-spi-nor-nand-flash-emmc-bga153-162-169-100-221-tsop-sop-plcc">T48 programmer</a> with the <a href="https://xgecu.myshopify.com/products/100-original-xgecu-adp_f48_ex-1-tsop48-special-adapter-for-nor-flash-only-use-on-t48-tl866-3g-programmer">TSOP48 adapter</a>.

### How to Program the Cartridges

<a href="https://github.com/MouseBiteLabs/Game-Boy-Cartridges/wiki">Check out the wiki for more information.</a>

## Battery Safety

When assembling a board, I recommend populating all the parts *except* the battery, and getting it to run initially without it. This is to make it easier to fix any solder connections that might need fixing, without having to worry about getting the battery hot. And if you need to rework anything near the battery after you've put it on the board, be safe and remove it before putting a hot soldering iron next to it.

If you're assembling these boards with a hot plate or hot air, *do not* solder the battery on this way. You should use an iron, and keep heat off of the battery as much as possible. 

(Also check polarity!)

## Board Configurations

The board comes with one set of jumper pads for solder bridges - SJ3.

### MBC3 Type Select (SJ3)

The MBC3 chip you use from the donor cartridge can be one of a few different types:

- If your MBC3 doesn't have a revision letter on it (it just says "MBC3" on it) then bridge the middle pad of SJ3 to the left. (You will also need to populate Q1!)
- If your MBC3 *does* have a revision letter, such as MBC3A or MBC3B, then bridge the middle pad of SJ3 to the right.

*[Images of MBC3 chips from <a href="https://gbhwdb.gekkio.fi/cartridges/mbc3.html">Game Boy Hardware Database</a>.]*

### Games Without a Real-Time Clock

If your game does *not* use the RTC function with the crystal X1, then you need to bridge the pads of Z1. You also do not need to populate the battery on the board.

## Test Points and Final Checkout

On the back of the board are five test points. Here's where they are connected:

- TP1: MBC3 supply voltage
- TP2: Battery voltage (after R1)
- TP3: Battery voltage (positive terminal of battery)
- TP4: Ground
- TP5: VCC input voltage

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
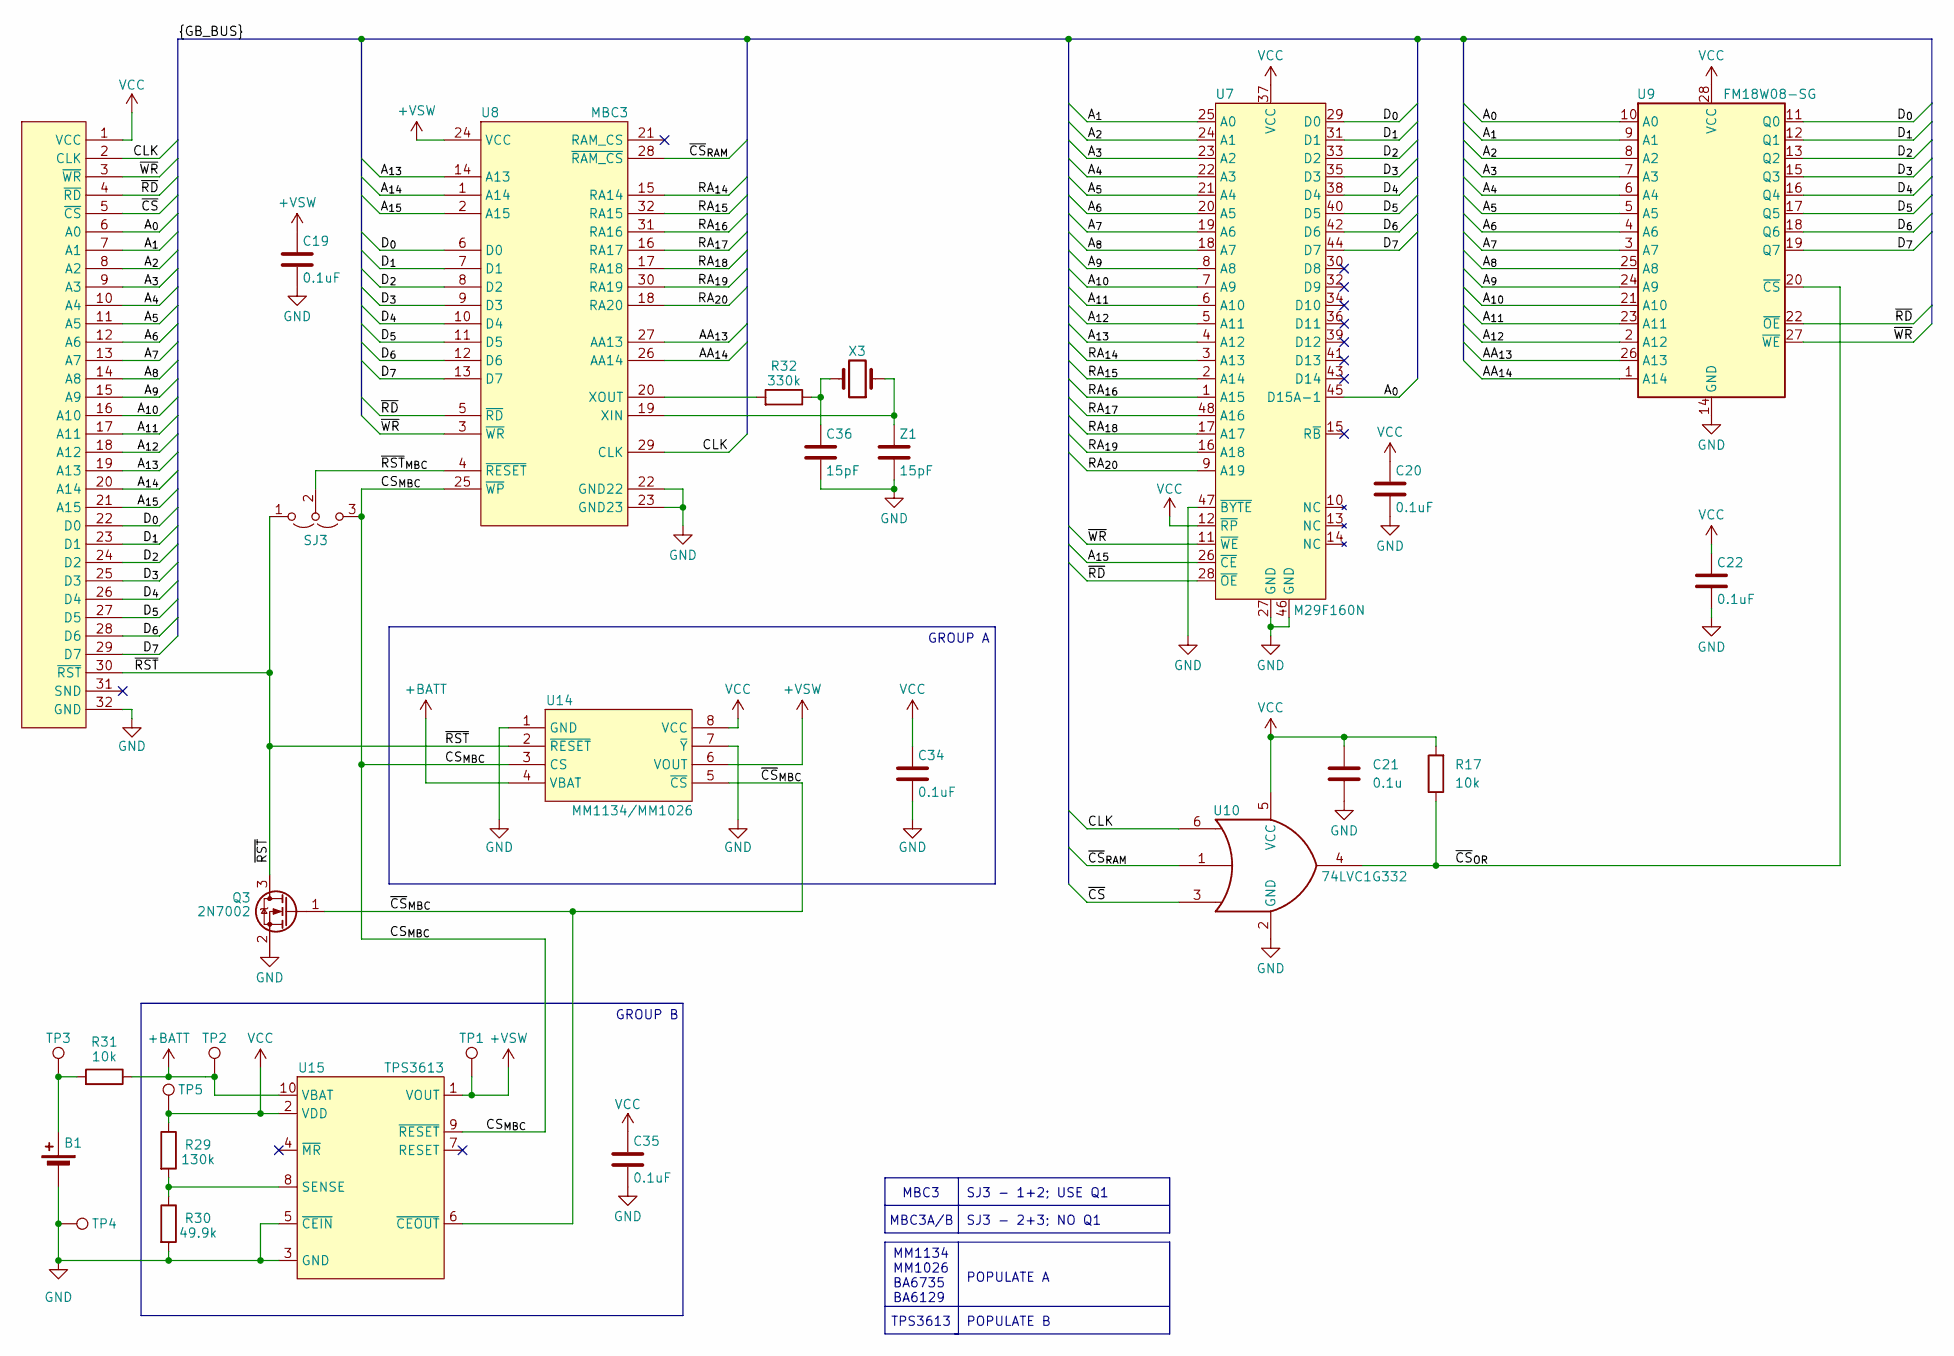
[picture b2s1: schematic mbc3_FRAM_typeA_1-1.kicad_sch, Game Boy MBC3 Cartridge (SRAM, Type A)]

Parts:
B1: CR2025
C19, C20, C22, C34, C35: 0.1uF; C_0603_1608Metric_Boxed
C21: 0.1u; C_0603_1608Metric_Boxed
C36: 15pF; C_0603_1608Metric_Boxed
P1: GBC_CARTTAB; GBC_CART_TABBED
Q3: 2N7002; SOT-23
R17, R31: 10k; R_0603_1608Metric_Boxed
R29: 130k; R_0603_1608Metric_Boxed
R30: 49.9k; R_0603_1608Metric_Boxed
R32: 330k; R_0603_1608Metric_Boxed
SJ3: SJ2W; SJ_2
TP1, TP2, TP3, TP4, TP5: TPB1,27; TestPoint_Pad_D1.0mm
U7: M29F160N; TSOP-I-48_18.4x12mm_P0.5mm
U8: MBC3; QFP-32
U9: FM18W08-SG; SO28
U10: 74LVC1G332; SOT-363_SC-70-6
U14: MM1134/MM1026; SOIC-8_3.9x4.9mm_P1.27mm
U15: TPS3613; MSOP-10_3x3mm_P0.5mm
X3: XTAL-3.2X1.5; XTAL3215
Z1: 15pF; C_0603_1608Metric_Boxed

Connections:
+BATT: R31.1, TP2.1, U14.4 (VBAT), U15.10 (VBAT)
+VSW: C19.1, TP1.1, U8.24 (VCC), U14.6 (VOUT), U15.1 (VOUT)
/AA_{13}: U8.27 (AA13), U9.26 (A13)
/AA_{14}: U8.26 (AA14), U9.1 (A14)
/A_{0}: P1.6 (A0), U7.45 (D15A-1), U9.10 (A0)
/A_{1}: P1.7 (A1), U7.25 (A0), U9.9 (A1)
/A_{2}: P1.8 (A2), U7.24 (A1), U9.8 (A2)
/A_{3}: P1.9 (A3), U7.23 (A2), U9.7 (A3)
/A_{4}: P1.10 (A4), U7.22 (A3), U9.6 (A4)
/A_{5}: P1.11 (A5), U7.21 (A4), U9.5 (A5)
/A_{6}: P1.12 (A6), U7.20 (A5), U9.4 (A6)
/A_{7}: P1.13 (A7), U7.19 (A6), U9.3 (A7)
/A_{8}: P1.14 (A8), U7.18 (A7), U9.25 (A8)
/A_{9}: P1.15 (A9), U7.8 (A8), U9.24 (A9)
/A_{10}: P1.16 (A10), U7.7 (A9), U9.21 (A10)
/A_{11}: P1.17 (A11), U7.6 (A10), U9.23 (A11)
/A_{12}: P1.18 (A12), U7.5 (A11), U9.2 (A12)
/A_{13}: P1.19 (A13), U7.4 (A12), U8.14 (A13)
/A_{14}: P1.20 (A14), U8.1 (A14)
/A_{15}: P1.21 (A15), U7.26 (~CE), U8.2 (A15)
/CLK: P1.2 (CLK), U8.29 (CLK), U10.6
/CS_{MBC}: SJ3.3 (B), U8.25 (~WP), U14.3 (CS), U15.9 (~RESET)
/D_{0}: P1.22 (D0), U7.29 (D0), U8.6 (D0), U9.11 (Q0)
/D_{1}: P1.23 (D1), U7.31 (D1), U8.7 (D1), U9.12 (Q1)
/D_{2}: P1.24 (D2), U7.33 (D2), U8.8 (D2), U9.13 (Q2)
/D_{3}: P1.25 (D3), U7.35 (D3), U8.9 (D3), U9.15 (Q3)
/D_{4}: P1.26 (D4), U7.38 (D4), U8.10 (D4), U9.16 (Q4)
/D_{5}: P1.27 (D5), U7.40 (D5), U8.11 (D5), U9.17 (Q5)
/D_{6}: P1.28 (D6), U7.42 (D6), U8.12 (D6), U9.18 (Q6)
/D_{7}: P1.29 (D7), U7.44 (D7), U8.13 (D7), U9.19 (Q7)
/RA_{14}: U7.3 (A13), U8.15 (RA14)
/RA_{15}: U7.2 (A14), U8.32 (RA15)
/RA_{16}: U7.1 (A15), U8.31 (RA16)
/RA_{17}: U7.48 (A16), U8.16 (RA17)
/RA_{18}: U7.17 (A17), U8.17 (RA18)
/RA_{19}: U7.16 (A18), U8.30 (RA19)
/RA_{20}: U7.9 (A19), U8.18 (RA20)
/~CS: P1.5 (~CS), U10.3
/~CS_{MBC}: Q3.1 (G), U14.5 (~CS), U15.6 (~CEOUT)
/~CS_{OR}: R17.1, U9.20 (~CS), U10.4
/~CS_{RAM}: U8.28 (~RAM_CS), U10.1
/~RD: P1.4 (~RD), U7.28 (~OE), U8.5 (~RD), U9.22 (~OE)
/~RST: P1.30 (~RST), Q3.3 (D), SJ3.1 (A), U14.2 (~RESET)
/~RST_{MBC}: SJ3.2 (C), U8.4 (~RESET)
/~WR: P1.3 (~WR), U7.11 (~WE), U8.3 (~WR), U9.27 (~WE)
GND: B1.2 (-), C19.2, C20.2, C21.2, C22.2, C34.2, C35.2, C36.2, P1.32 (GND), Q3.2 (S), R30.2, TP4.1, U7.27 (GND), U7.46 (GND), U7.47 (~BYTE), U8.22 (GND22), U8.23 (GND23), U9.14 (GND), U10.2 (GND), U14.1 (GND), U14.7 (~Y), U15.3 (GND), U15.5 (~CEIN), Z1.2
unnamed: B1.1 (+), R31.2, TP3.1
unnamed: C36.1, R32.1, X3.2
unnamed: U8.19 (XIN), X3.1, Z1.1
unnamed: R32.2, U8.20 (XOUT)
unnamed: R29.2, R30.1, U15.8 (SENSE)
VCC: C20.1, C21.1, C22.1, C34.1, C35.1, P1.1 (VCC), R17.2, R29.1, TP5.1, U7.12 (~RP), U7.37 (VCC), U9.28 (VCC), U10.5 (VCC), U14.8 (VCC), U15.2 (VDD)

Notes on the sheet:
MM1134 MM1026 BA6735 BA6129
SJ3 - 2+3; NO Q1
GROUP A
POPULATE A
TPS3613
POPULATE B
GROUP B
SJ3 - 1+2; USE Q1
MBC3
MBC3A/B

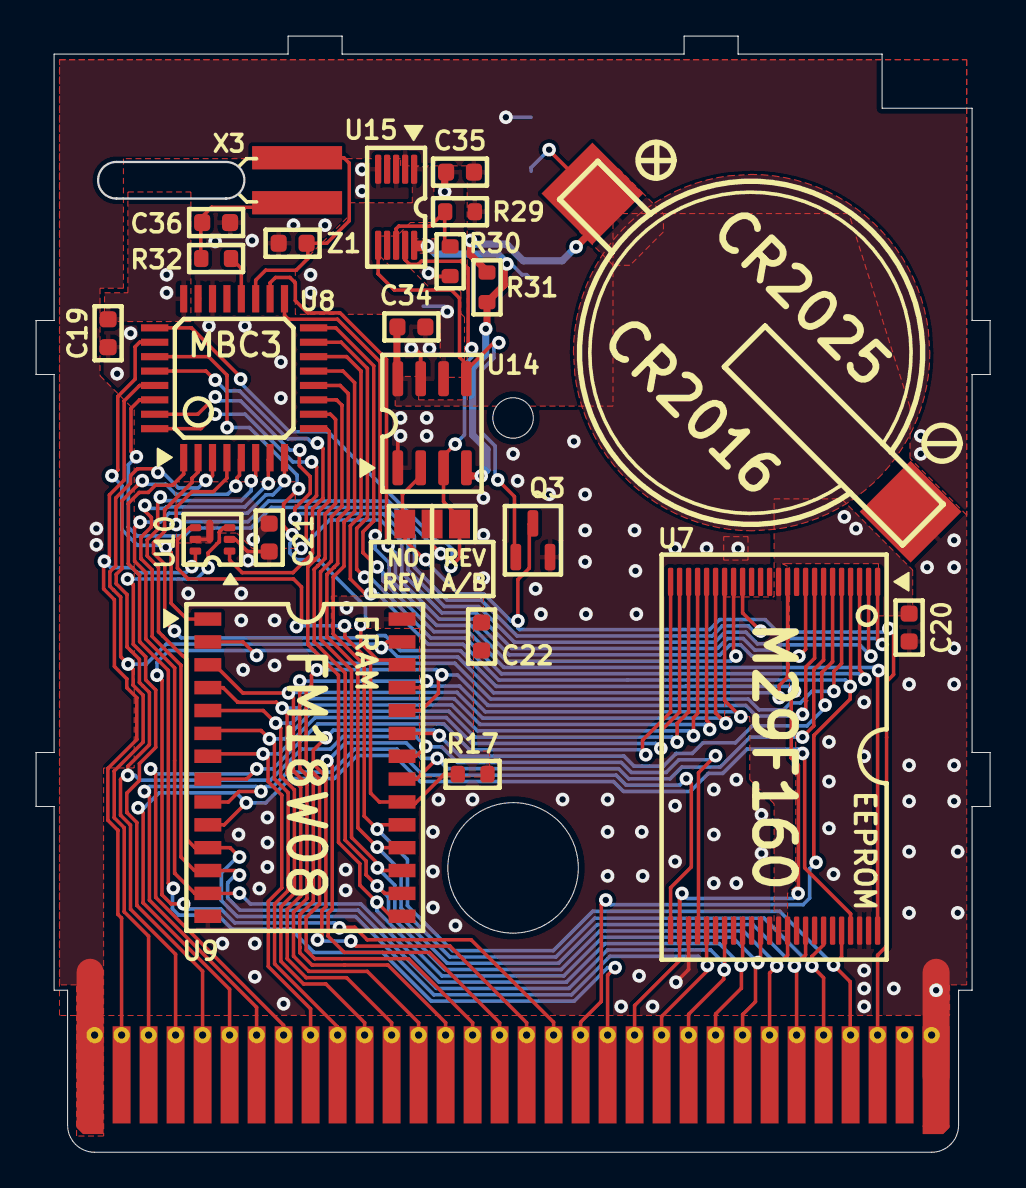
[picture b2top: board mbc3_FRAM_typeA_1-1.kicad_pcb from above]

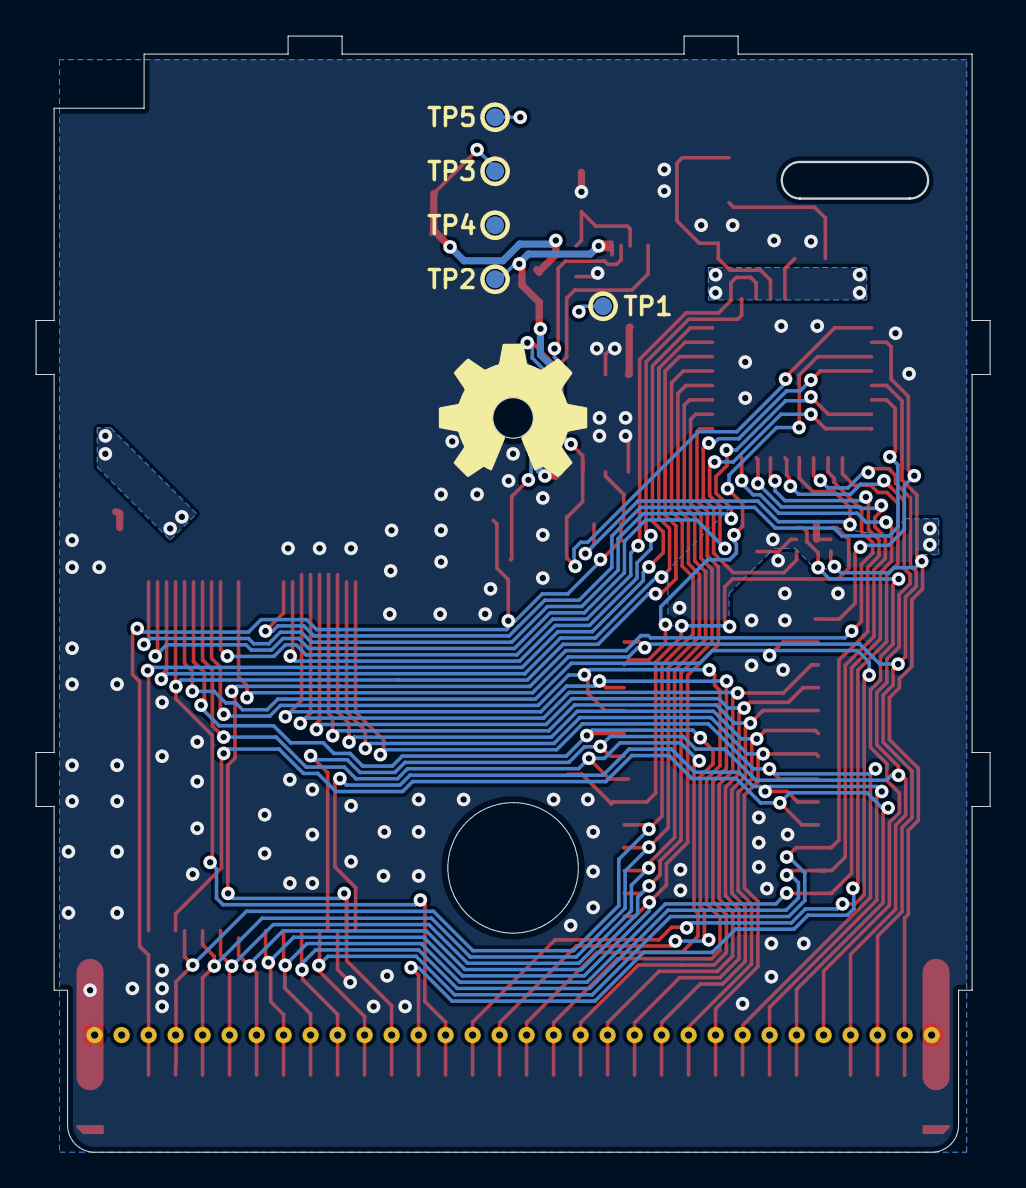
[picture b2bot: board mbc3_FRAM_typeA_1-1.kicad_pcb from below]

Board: 2 copper layers, 53.0 x 62.0 mm, 29 parts (5 on the bottom side), 52 nets.

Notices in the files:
MBC1 (Type A, SRAM)/README.md:
This work is licensed under a Creative Commons Attribution-ShareAlike 4.0 International License. You are able to copy and redistribute the material in any medium or format, as well as remix, transform, or build upon the material for any purpose (even commercial) - but you **must** give appropriate credit, provide a link t
©MouseBiteLabs 2025
